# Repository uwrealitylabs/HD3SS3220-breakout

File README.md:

# HD3SS3220 USB-C Mux Test Board

This is a project designed to bridge the gap between our FPGA board and modern USB-C devices, offering a great look into how the devices we interact with daily actually work under the hood! 

This test board utilizes the **HD3SS3220RNHR USB-C Multiplexer** to validate USB 3.0 functionality from our FPGA board's USB interface chip, effectively bridging a USB 3.0 Type-A (female) connection to a USB-C (female) connection. 

## 📸 Project Previews

**3D Render & PCB Layout:**
<br>

<br><br>

**Schematics:**

---

## ⚙️ Architecture & Configuration Notes
* **Configurable DRP, UFP and DFP Implementation:** Configured for Dual-Role Port, Downstream Facing Port and Upstream Facing Port functionality (refer to Section 4 of the HD3SS3220 datasheet).
* **Always-On Operation:** The chip automatically wakes up and cannot be disabled via a computer, as `ENn_CC` is tied directly to ground.
* **Power Constraints:** VBUS_DET and VDD5 are kept separate (though they default to 5V, power negotiation causes voltage variations). Currently, the board requires an **external 5V power source**.

---

## 📏 High-Speed Routing Constraints (USB 3.0)

To ensure 5 Gbps signal integrity, the following rigid design rules were implemented during layout:

### 1. Differential Pair Routing & Symmetry
* **Intrapair Matching:** Length matching is strictly intrapair (TX+ to TX-, RX+ to RX-). TX and RX pairs do not need to match each other. Serpentine routing is applied as close to the mismatched ends as possible.
* **Symmetry:** High-speed pairs are purely symmetrical. Any IC breakout mismatch is resolved within 0.25 inches of the package.
* **Via Management:** Vias are minimized. Any unavoidable layer transitions ensure via stubs are kept under **15 mils** (back-drilled if necessary).

### 2. Clearances & Spacing
* **5W Rule:** Maintained a spacing of at least 5x the trace width between different high-speed signal pairs.
* **Keep-Outs:** Maintained >30 mils clearance from normal signals, and >50 mils from clocks/oscillators (not that we have one).
* **Plane Edges:** Traces are routed at least 90 mils away from the edge of the GND reference plane, and at least 1.5W away from any generic plane voids.

### 3. ESD Protection & Signal Path
* **ESD Placement:** TPD2EUSB30 / TPD4EUSB30 diodes are placed immediately at the USB connector.
* **Geometry:** Flow-through routing only (no stubs). Sharp bends are eliminated using large-radii rounded corners to prevent E-field buildup.
* **Test Points:** Strictly **NO** test points on high-speed pairs.

### 4. AC Coupling Capacitors
* **Footprints:** Symmetrically placed **0402** packages.

---

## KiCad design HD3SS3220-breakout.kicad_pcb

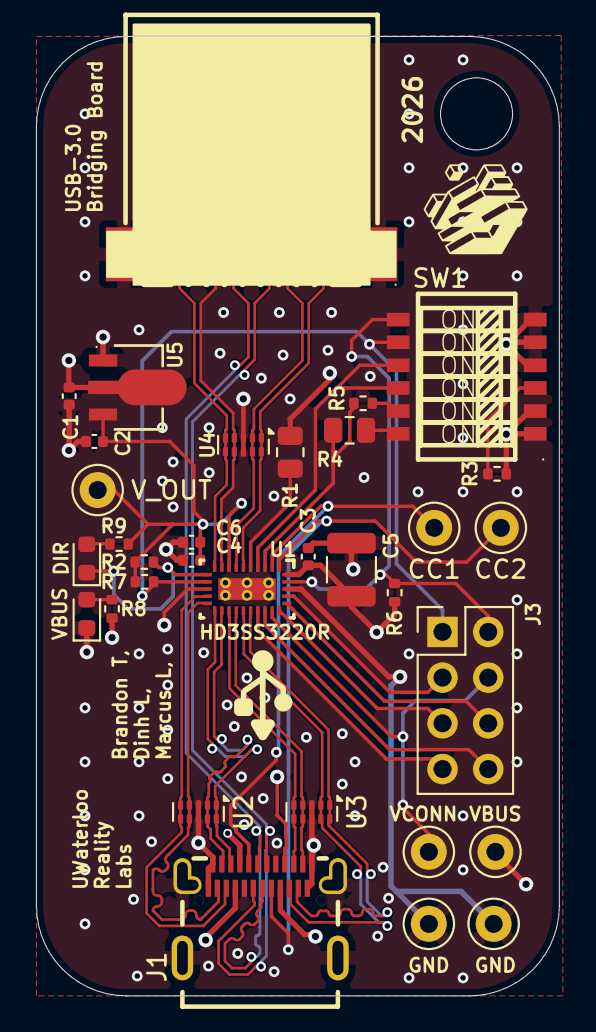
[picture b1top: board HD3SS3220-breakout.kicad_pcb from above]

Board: 4 copper layers, 29.0 x 53.3 mm, 33 parts (0 on the bottom side), 36 nets.

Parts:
C1, C2: 10uF; C_0402_1005Metric
C3, C4: 100nF; C_0402_1005Metric
C5: 100uF; C_1210_3225Metric
C6: 1uF; C_0402_1005Metric
CC1: CC1; TestPoint_Keystone_5000-5004_Miniature
CC2: CC2; TestPoint_Keystone_5000-5004_Miniature
DIR: LED; LED_0603_1608Metric
GND: GND2; TestPoint_Keystone_5000-5004_Miniature
GND#2: GND1; TestPoint_Keystone_5000-5004_Miniature
J1: USB_C_Receptacle; USB-C-SMD_TYPEC-324G-BCP24
J2: U-A-39SS-Y-1; USB-3.0-A_U-A-39SS-Y-1
J3: A2541WV-2x4P; PinHeader_2x04_P2.54mm_Vertical
R1: 900K; R_0805_2012Metric
R2: 200K; R_0402_1005Metric
R3: 1K; R_0402_1005Metric
R4: 500K; R_0805_2012Metric
R5, R6, R7: 10K; R_0402_1005Metric
R8, R9: 1k; R_0402_1005Metric
SW1: DSHP06TSGER_C3293146; SW-SMD_12P-L9.2-W5.4-P1.27-LS8.5
U1: HD3SS3220RNHR; HD3SS3220IRNHR
U2, U3, U4: TPD4EUSB30; USON-10_2.5x1.0mm_P0.5mm
U5: HT7533-1_C14289; SOT-89-3_L4.5-W2.5-P1.50-LS4.2-BR
VBUS: LED; LED_0603_1608Metric
VBUS#2: VBUS; TestPoint_Keystone_5000-5004_Miniature
VCONN: VCONN; TestPoint_Keystone_5000-5004_Miniature
V_OUT: VCC33; TestPoint_Keystone_5000-5004_Miniature

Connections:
/ADDR: J3.7, U1.22 (ADDR)
/CC1: CC1.1 (1_1), J1.A5 (CC1), U1.2 (CC1)
/CC2: CC2.1 (1_1), J1.B5 (CC2), U1.1 (CC2)
/D+: J1.A6 (DP1), J1.B6 (DP2), J2.3 (D+)
/D-: J1.A7 (DN1), J1.B7 (DN2), J2.2 (D-)
/DIR: DIR.1 (K), R2.2, U1.11 (DIR)
/ENn_CC: J3.2, R6.2, SW1.7 (B6), U1.29 (ENn_CC)
/ENn_Mux: J3.1, R7.2, SW1.8 (B5), U1.12 (ENn_MUX)
/ID: J3.3, U1.27 (ID)
/INT_N: J3.8, U1.23 (INT_N/OUT3)
/MODE: R4.2, R5.2, U1.3 (CURRENT_MODE)
/PORT: SW1.9 (B4), SW1.10 (B3), U1.4 (PORT)
/RX1+: J1.B11 (SSRXp1), U1.15 (RX1+), U2.4 (D2+), U2.7 (NC)
/RX1-: J1.B10 (SSRXn1), U1.14 (RX1-), U2.5 (D2-), U2.6 (NC)
/RX2+: J1.A11 (SSRXp2), U1.19 (RX2+), U3.4 (D2+), U3.7 (NC)
/RX2-: J1.A10 (SSRXn2), U1.18 (RX2+), U3.5 (D2-), U3.6 (NC)
/SCL: J3.6, U1.26 (SCL/OUT2)
/SDA: J3.5, U1.25 (SDA/OUT1)
/SSRX+: J2.6 (STDA_SSRX+), U1.9 (RXp), U4.4 (D2+), U4.7 (NC)
/SSRX-: J2.5 (STDA_SSRX-), U1.10 (RXn), U4.5 (D2-), U4.6 (NC)
/SSTX+: J2.9 (STDA_SSTX+), U1.6 (TXp), U4.1 (D1+), U4.10 (NC)
/SSTX-: J2.8 (STDA_SSTX-), U1.7 (TXn), U4.2 (D1-), U4.9 (NC)
/TX1+: J1.A2 (SSTXP1), U1.17 (TX1+), U2.2 (D1-), U2.9 (NC)
/TX1-: J1.A3 (SSTXn1), U1.16 (TX1-), U2.1 (D1+), U2.10 (NC)
/TX2+: J1.B2 (SSTXp2), U1.21 (TX2+), U3.1 (D1+), U3.10 (NC)
/TX2-: J1.B3 (SSTXn2), U1.20 (TX2-), U3.2 (D1-), U3.9 (NC)
/VBUS_DET: R1.2, U1.5 (VBUS_DET)
/VCONN: J3.4, U1.24 (VCONN_FAULT_N), VCONN.1 (1_1)
GND: C1.2, C2.2, C3.1, C4.1, C5.1, C6.1, GND.1 (1_1), GND#2.1 (1_1), J1.1 (EP), J1.2 (EP), J1.3 (EP), J1.4 (EP), J1.A1 (GND), J1.A12 (GND), J1.B1 (GND), J1.B12 (GND), J2.4 (GND), J2.7 (GND), J2.10 (GND), J2.11 (GND), SW1.4 (A4), SW1.5 (A5), SW1.6 (A6), U1.13 (GND), U1.28 (GND), U1.31 (EP), U2.3 (GND), U2.8 (GND), U3.3 (GND), U3.8 (GND), U4.3 (GND), U4.8 (GND), U5.1 (GND), VBUS.1 (K)
unnamed: DIR.2 (A), R9.2
unnamed: R3.2, SW1.3 (A3)
unnamed: R4.1, SW1.12 (B1)
unnamed: R5.1, SW1.11 (B2)
unnamed: R8.2, VBUS.2 (A)
VBUS: C1.1, C3.2, C5.2, J1.A4 (VBUS), J1.A9 (VBUS), J1.B4 (VBUS), J1.B9 (VBUS), J2.1 (VBUS), R1.1, R3.1, R6.1, R8.1, SW1.1 (A1), SW1.2 (A2), U1.30 (VDD5), U5.2 (Vin), VBUS#2.1 (1_1)
V_OUT: C2.1, C4.2, C6.2, R2.1, R7.1, R9.1, U1.8 (VCC33), U5.3 (Vout), V_OUT.1 (1_1)

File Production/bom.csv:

"Designator","Value","Footprint","Quantity","LCSC","LCSC Part","MPN","Manufacturer"
"C1,C2","10uF","Capacitor_SMD:C_0402_1005Metric","2","C7472949","","",""
"C3,C4","100nF","Capacitor_SMD:C_0402_1005Metric","2","C106204","","",""
"C5","100uF","Capacitor_SMD:C_1210_3225Metric","1","C394395","","",""
"C6","1uF","Capacitor_SMD:C_0402_1005Metric","1","C106204","","",""
"DIR_LED2,VBUS_LED2","LED","LED_SMD:LED_0603_1608Metric","2","C375576","","",""
"J1","USB_C_Receptacle","Interface_USB:USB-C-SMD_TYPEC-324G-BCP24","1","C920230","","",""
"J2","U-A-39SS-Y-1","Interface_USB:USB-3.0-A_U-A-39SS-Y-1","1","C530639","","",""
"J3","A2541WV-2x4P","Connector_PinHeader_2.54mm:PinHeader_2x04_P2.54mm_Vertical","1","C225519","","",""
"R1","900K","Resistor_SMD:R_0805_2012Metric","1","C52209984","","",""
"R2","200K","Resistor_SMD:R_0402_1005Metric","1","C413111","","",""
"R3","1K","Resistor_SMD:R_0402_1005Metric","1","C242161","","",""
"R4","500K","Resistor_SMD:R_0805_2012Metric","1","C316218","","",""
"R5-R7","10K","Resistor_SMD:R_0402_1005Metric","3","C413111","","",""
"R8,R9","1k","Resistor_SMD:R_0402_1005Metric","2","C242161","","",""
"SW1","DSHP06TSGER_C3293146","UWReality_Labs:SW-SMD_12P-L9.2-W5.4-P1.27-LS8.5","1","","C3293146","DSHP06TSGER","康深"
"TP1","VBUS","TestPoint:TestPoint_Keystone_5000-5004_Miniature","1","","","",""
"TP2","VCONN","TestPoint:TestPoint_Keystone_5000-5004_Miniature","1","","","",""
"TP3","VCC33","TestPoint:TestPoint_Keystone_5000-5004_Miniature","1","","","",""
"TP4","GND1","TestPoint:TestPoint_Keystone_5000-5004_Miniature","1","","","",""
"TP5","GND2","TestPoint:TestPoint_Keystone_5000-5004_Miniature","1","","","",""
"TP6","CC2","TestPoint:TestPoint_Keystone_5000-5004_Miniature","1","","","",""
"TP7","CC1","TestPoint:TestPoint_Keystone_5000-5004_Miniature","1","","","",""
"U1","HD3SS3220RNHR","Interface_USB:HD3SS3220IRNHR","1","C165155","","",""
"U2-U4","TPD4EUSB30","Package_SON:USON-10_2.5x1.0mm_P0.5mm","3","C90627","","",""
"U5","HT7533-1_C14289","Interface_USB:SOT-89-3_L4.5-W2.5-P1.50-LS4.2-BR","1","C14289","","",""

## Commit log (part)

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2026-02-20 First draft schematic + notes
2026-02-23 Net labels
2026-02-24 further reorganizaing
2026-02-26 switches and ldo
2026-02-28 power glag
2026-02-28 added submodule library
2026-02-28 post review on 02/27/2026
2026-02-28 new library
2026-02-28 usb-a 3.0 connector
2026-02-28 all reorged
2026-02-28 notes
2026-03-06 more stuff
2026-03-11 new files
2026-03-13 trace info
2026-03-16 new pcb stuff
2026-03-26 Added indicator LED's and test points
2026-03-29 pain and suffering
2026-03-29 Fixed footprint pad naming issues
2026-03-31 Added dip switch footprint to library and PCB editor
2026-04-03 added more footprints
2026-04-04 Fixed mux footprint somewhat, starting to route
2026-04-08 routing
2026-04-27 cursed vias
2026-05-29 Schematic Hierarchy Implementation
2026-05-30 Hierarchy Schematic Implementation and Clean-up (Please Refer to this Version for previous sym-lib-table)
2026-05-31 Routing Complete (DRC Checker Errors needs fixing)
2026-06-01 DRC Errors Fixed, BOM Cleaned up and Generated, Gerber Generated
2026-06-02 Hopefully final DRC error fixed by reducing Minimum Spoke Count from 2 to 1
2026-06-02 Add Screenshots for README
2026-06-02 Add README for HD3SS3220 USB-C Mux Test Board
2026-06-02 Revise schematic images and descriptions in README
    Updated schematic images in README with new descriptions.
2026-06-02 Remove plane voiding information from README
    Removed plane voiding details for AC coupling capacitors.
2026-06-03 Protruding USB connectors for easier CAD design
2026-06-04 Holes drilled for easier case CAD design
2026-06-07 Added missing components (Coupling capacitors and led resistors, wired board again
2026-06-10 Schematic Review: Removed Coupling Capacitors (no USB controller just mux)
2026-06-12 Rerouted for new elements added (5 DRC errors left)
2026-06-12 Screenshot Updated
2026-06-12 Revise schematics and add filled PCB layout image
    Updated schematics section in README and added filled PCB layout image.
2026-06-12 Add filled PCB layout image to README
2026-06-12 Update project previews section in README
    Fixed formatting for project previews in README.
2026-06-12 Correct image formatting in README
    Fixed formatting issues in project previews section.
2026-06-12 Add project preview section to README
2026-06-12 Clean up line breaks in README.md
    Removed unnecessary line breaks in project previews section.
2026-06-14 Rerouting PCB after fixes on schematic, fixed subsequent DRC errors
2026-06-15 Generated Gerber files and proper BOM
2026-06-28 Corrected ESD Diodes logic
